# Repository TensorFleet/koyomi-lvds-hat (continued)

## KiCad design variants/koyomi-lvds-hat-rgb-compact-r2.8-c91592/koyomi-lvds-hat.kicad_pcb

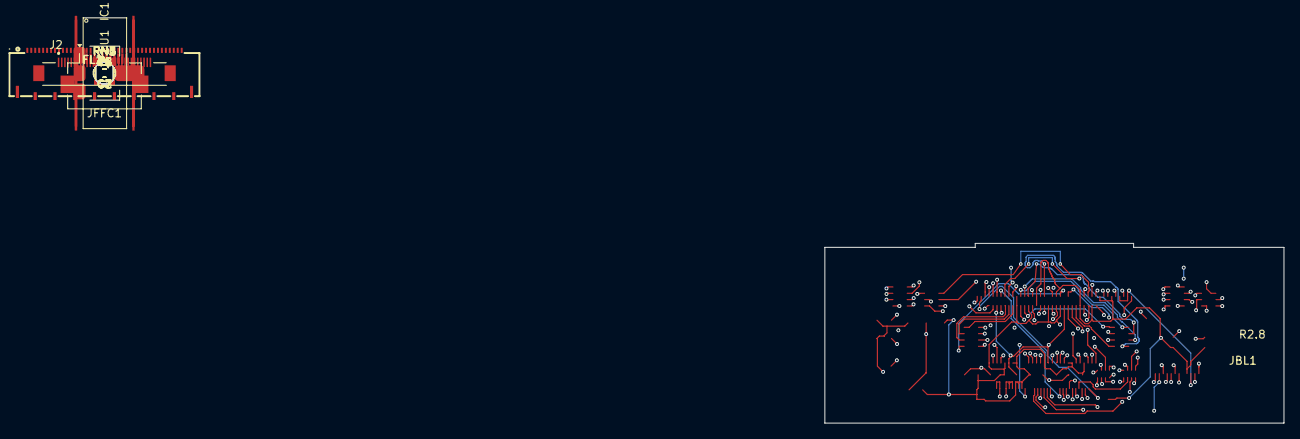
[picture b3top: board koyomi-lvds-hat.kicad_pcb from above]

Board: 4 copper layers, 58.0 x 22.7 mm, 29 parts (0 on the bottom side), 78 nets.

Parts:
C1, C4: 1uF; C_0603_1608Metric_Pad1.08x0.95mm_HandSolder
C2, C5: 100nF; C_0603_1608Metric_Pad1.08x0.95mm_HandSolder
C3, C6: 10nF; C_0603_1608Metric_Pad1.08x0.95mm_HandSolder
C7, C8: 4.7uF; C_0603_1608Metric_Pad1.08x0.95mm_HandSolder
FL1, FL2: DLP2ADN900HL4L; Murata_DLP2ADN121HL4L
H1, H2, H3, H4: MountingHole; RPi_Hat_Mounting_Hole
IC1: SN75LVDS83B; TSSOP56
J2: 20374-R30E-31; I-PEX_20374-R30E-31
JBL1: BACKLIGHT FFC-12; Hirose_FH12-12S-0.5SH_1x12-1MP_P0.50mm_Horizontal
JFFC1: FH41-40S-0.5SH(05) / C596805; FPC-SMD_FH41-40S-0.5SH
JP1: CLKSEL; SolderJumper-2_P1.3mm_Open_RoundedPad1.0x1.5mm
JP2: SHTDN; SolderJumper-2_P1.3mm_Open_RoundedPad1.0x1.5mm
R1, R2: 4.7K; R_0603_1608Metric_Pad0.98x0.95mm_HandSolder
RN1, RN2, RN3, RN4, RN5, RN6: 47; R_Array_Convex_4x0603
U1: AP2114H-2.5; SOT-223-3_TabPin2

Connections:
+2V5: C4.1, C5.1, C6.1, C8.1, J2.4, J2.5, J2.6, U1.2 (VO)
+3V3: C1.1, C2.1, C3.1, C7.1, IC1.1 (IOVCC@1), IC1.9 (VCC@1), IC1.26 (IOVCC@2), IC1.34 (PLLVCC), IC1.44 (LVDSVCC), JFFC1.1 (3.3V), R1.1, R2.1, U1.3 (VI)
+5V: JBL1.10, JFFC1.2 (5V), JFFC1.4 (5V)
B0: JFFC1.7 (BCM4_GPCLK0), RN1.7 (R2.2)
B1: JFFC1.29 (BCM5), RN4.8 (R1.2)
B2: JFFC1.31 (BCM6), RN5.5 (R4.2)
B3: JFFC1.26 (BCM7_CE1), RN3.8 (R1.2)
B4: JFFC1.24 (BCM8_CE0), RN3.7 (R2.2)
B5: JFFC1.21 (BCM9_MISO), RN3.6 (R3.2)
CLKIN: JFFC1.27 (BCM0_ID_SD), RN4.7 (R2.2)
CLKSEL: IC1.17 (CLKSEL), JP1.1 (A), R1.2
D0: IC1.51 (D0), RN5.1 (R1.1)
D1: IC1.52 (D1), RN2.3 (R3.1)
D2: IC1.54 (D2), RN2.2 (R2.1)
D3: IC1.55 (D3), RN6.4 (R4.1)
D4: IC1.56 (D4), RN6.3 (R3.1)
D6: IC1.3 (D6), RN6.2 (R2.1)
D7: IC1.4 (D7), RN3.5 (R4.2)
D8: IC1.6 (D8), RN4.4 (R4.1)
D9: IC1.7 (D9), RN5.3 (R3.1)
D12: IC1.11 (D12), RN5.2 (R2.1)
D13: IC1.12 (D13), RN1.1 (R1.1)
D14: IC1.14 (D14), RN2.4 (R4.1)
D15: IC1.15 (D15), RN1.2 (R2.1)
D18: IC1.19 (D18), RN4.1 (R1.1)
D19: IC1.20 (D19), RN5.4 (R4.1)
D20: IC1.22 (D20), RN3.1 (R1.1)
D21: IC1.23 (D21), RN3.2 (R2.1)
D22: IC1.24 (D22), RN3.3 (R3.1)
D24: IC1.27 (D24), RN1.3 (R3.1)
D25: IC1.28 (D25), RN1.4 (R4.1)
D26: IC1.30 (D26), RN4.3 (R3.1)
EN: JBL1.12, JFFC1.13 (BCM27)
ENABLE: JFFC1.28 (BCM1_ID_SC), RN4.6 (R3.2)
G0: JFFC1.19 (BCM10_MOSI), RN3.4 (R4.1)
G1: JFFC1.23 (BCM11_SCLK), RN4.5 (R4.2)
G2: JFFC1.32 (BCM12_PWM0), RN5.6 (R3.2)
G3: JFFC1.33 (BCM13_PWM1), RN5.7 (R2.2)
G4: JFFC1.8 (BCM14_TXD), RN1.8 (R1.2)
G5: JFFC1.10 (BCM15_RXD), RN2.5 (R4.2)
GND: C1.2, C2.2, C3.2, C4.2, C5.2, C6.2, C7.2, C8.2, IC1.2 (D5), IC1.5 (GND@1), IC1.8 (D10), IC1.10 (D11), IC1.13 (GND@2), IC1.16 (D16), IC1.18 (D17), IC1.21 (GND@3), IC1.25 (D23), IC1.29 (GND@4), IC1.33 (GND@5), IC1.35 (GND@6), IC1.36 (GND@7), IC1.43 (GND@8), IC1.49 (GND@9), IC1.50 (D27), IC1.53 (GND@10), J2.7, J2.8, J2.9, J2.S1 (SHIELD), J2.S2 (SHIELD__1), JBL1.9, JFFC1.6 (GND), JFFC1.9 (GND), JFFC1.14 (GND), JFFC1.20 (GND), JFFC1.25 (GND), JFFC1.30 (GND), JP1.2 (B), JP2.2 (B), U1.1 (GND)
HSYNC: JFFC1.5 (BCM3_SCL), RN1.6 (R3.2)
LCD_INS: J2.30, JFFC1.39 (GND)
L_CLKIN: IC1.31 (CLKIN), RN4.2 (R2.1)
unnamed: FL2.3, IC1.40 (CLCKOUTM)
unnamed: FL2.1, IC1.39 (CLCKOUTP)
unnamed: FL1.7, IC1.48 (Y0M)
unnamed: FL1.5, IC1.47 (Y0P)
unnamed: FL1.3, IC1.46 (Y1M)
unnamed: FL1.1, IC1.45 (Y1P)
unnamed: FL2.7, IC1.42 (Y2M)
unnamed: FL2.5, IC1.41 (Y2P)
PANEL_ID0: J2.10, JFFC1.17 (3.3V)
PANEL_ID1: J2.21, JFFC1.34 (GND)
PWM: JBL1.11, JFFC1.37 (BCM26)
R0: JFFC1.36 (BCM16), RN5.8 (R1.2)
R1: JFFC1.11 (BCM17), RN2.6 (R3.2)
R2: JFFC1.12 (BCM18_PCM_C), RN2.7 (R2.2)
R3: JFFC1.35 (BCM19_MISO_PCM_FS), RN6.5 (R4.2)
R4: JFFC1.38 (BCM20_MOSI_PCM_DI), RN6.6 (R3.2)
R5: JFFC1.40 (BCM21_SCLK_PCM_DO), RN6.7 (R2.2)
RX0+: FL1.6, J2.28
RX0-: FL1.8, J2.29
RX1+: FL1.2, J2.26
RX1-: FL1.4, J2.27
RX2+: FL2.6, J2.24
RX2-: FL2.8, J2.25
RXCLK+: FL2.2, J2.22
RXCLK-: FL2.4, J2.23
SHTDN: IC1.32 (~SHTDN), JP2.1 (A), R2.2
VAD: J2.1, J2.2, JBL1.7
VCD1: J2.18, JBL1.6
VCD2: J2.17, JBL1.5
VCD3: J2.16, JBL1.4
VCD4: J2.15, JBL1.3
VCD5: J2.14, JBL1.2
VCD6: J2.13, JBL1.1
VSYNC: JFFC1.3 (BCM2_SDA), RN1.5 (R4.2)

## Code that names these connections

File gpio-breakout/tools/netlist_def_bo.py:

"""GPIO breakout: FH41-40S FFC (carrier JDISP1/JFFC1 system) <-> Pi 40-pin header.

Straight-through pins 1..40 EXCEPT 17/34/39, which are isolated behind solder
jumpers: on a stock Pi those pins are 3V3/GND/GND, but the FFC system assigns
them PANEL_ID0/PANEL_ID1/LCD_INS. Jumpers default OPEN; test pads expose the
FFC-side nets for strapping or probing.
"""

NC = '__NC__'

# Pi header net names, physical pins 1..40 (standard map)
PI = {
    1: '+3V3', 2: '+5V', 3: 'GPIO2', 4: '+5V', 5: 'GPIO3', 6: 'GND',
    7: 'GPIO4', 8: 'GPIO14', 9: 'GND', 10: 'GPIO15', 11: 'GPIO17', 12: 'GPIO18',
    13: 'GPIO27', 14: 'GND', 15: 'GPIO22', 16: 'GPIO23', 17: '+3V3', 18: 'GPIO24',
    19: 'GPIO10', 20: 'GND', 21: 'GPIO9', 22: 'GPIO25', 23: 'GPIO11', 24: 'GPIO8',
    25: 'GND', 26: 'GPIO7', 27: 'ID_SD', 28: 'ID_SC', 29: 'GPIO5', 30: 'GND',
    31: 'GPIO6', 32: 'GPIO12', 33: 'GPIO13', 34: 'GND', 35: 'GPIO19', 36: 'GPIO16',
    37: 'GPIO26', 38: 'GPIO20', 39: 'GND', 40: 'GPIO21',
}
SPECIAL = {17: 'PANEL_ID0', 34: 'PANEL_ID1', 39: 'LCD_INS'}

ffc_map = {}
for n in range(1, 41):
    ffc_map[str(n)] = SPECIAL.get(n, PI[n])
ffc_map['1'] = '+3V3_FFC'
ffc_map['2'] = '+5V_FFC'
ffc_map['4'] = '+5V_FFC'
for n in range(41, 50):          # shield / mounting pins
    ffc_map[str(n)] = 'GND'

hdr_map = {str(n): PI[n] for n in range(1, 41)}

COMPONENTS = [
    ('J1', 'B2_INTERCONNECT:FH41-40S-0.5SH', 'FH41-40S-0.5SH(05)',
     'B2_INTERCONNECT:FPC-SMD_FH41-40S-0.5SH', ffc_map,
     {'lcsc': 'C596805', 'desc': 'carrier/LCD system FFC, bottom contact'}),
    ('J2', 'Connector_Generic:Conn_02x20_Odd_Even', 'Pi GPIO 2x20',
     'Connector_PinHeader_2.54mm:PinHeader_2x20_P2.54mm_Vertical', hdr_map,
     {'desc': 'fit stacking socket to ride a Pi, or pin header for cables'}),
    ('JP1', 'Jumper:SolderJumper_2_Open', 'ID0-3V3',
     'Jumper:SolderJumper-2_P1.3mm_Open_RoundedPad1.0x1.5mm',
     {'1': 'PANEL_ID0', '2': '+3V3'}, {'desc': 'close = FFC17 to Pi 3V3 (STRAP HIGH)'}),
    ('JP2', 'Jumper:SolderJumper_2_Open', 'ID1-GND',
     'Jumper:SolderJumper-2_P1.3mm_Open_RoundedPad1.0x1.5mm',
     {'1': 'PANEL_ID1', '2': 'GND'}, {'desc': 'close = FFC34 to GND (STRAP LOW)'}),
    ('JP3', 'Jumper:SolderJumper_2_Open', 'INS-GND',
     'Jumper:SolderJumper-2_P1.3mm_Open_RoundedPad1.0x1.5mm',
     {'1': 'LCD_INS', '2': 'GND'}, {'desc': 'close = FFC39 to GND (report inserted)'}),
    ('F1', 'Device:Polyfuse', '0.5A polyfuse 1206',
     'Fuse:Fuse_1206_3216Metric', {'1': '+5V_LNK', '2': '+5V_FFC'},
     {'lcsc': 'C106264', 'desc': 'PTC resettable, 0.5 A hold — FFC contact rating (SMD1206P050TF/15; alt C315893)'}),
    ('JP4', 'Jumper:SolderJumper_2_Bridged', '5V LINK',
     'Jumper:SolderJumper-2_P1.3mm_Bridged_RoundedPad1.0x1.5mm',
     {'1': '+5V', '2': '+5V_LNK'}, {'desc': 'CUT when LCD chain is powered externally'}),
    ('JP5', 'Jumper:SolderJumper_2_Bridged', '3V3 LINK',
     'Jumper:SolderJumper-2_P1.3mm_Bridged_RoundedPad1.0x1.5mm',
     {'1': '+3V3', '2': '+3V3_FFC'}, {'desc': 'CUT when LCD chain is powered externally'}),
    ('TP1', 'Connector:TestPoint', 'PANEL_ID0',
     'TestPoint:TestPoint_Pad_1.5x1.5mm', {'1': 'PANEL_ID0'}, {}),
    ('TP2', 'Connector:TestPoint', 'PANEL_ID1',
     'TestPoint:TestPoint_Pad_1.5x1.5mm', {'1': 'PANEL_ID1'}, {}),
    ('TP3', 'Connector:TestPoint', 'LCD_INS',
     'TestPoint:TestPoint_Pad_1.5x1.5mm', {'1': 'LCD_INS'}, {}),
    ('TP4', 'Connector:TestPoint', 'GND',
     'TestPoint:TestPoint_Pad_1.5x1.5mm', {'1': 'GND'}, {}),
    ('TP5', 'Connector:TestPoint', '3V3',
     'TestPoint:TestPoint_Pad_1.5x1.5mm', {'1': '+3V3'}, {}),
    ('H1', 'Mechanical:MountingHole', 'M2.5',
     'MountingHole:MountingHole_2.7mm_M2.5', None, {}),
    ('H2', 'Mechanical:MountingHole', 'M2.5',
     'MountingHole:MountingHole_2.7mm_M2.5', None, {}),
]

PWR_FLAGS = [
    ('#FLG1', '+3V3'), ('#FLG2', '+5V'), ('#FLG3', 'GND'),
]

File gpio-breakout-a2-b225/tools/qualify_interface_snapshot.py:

"""Independent schematic XML versus native PCB-pad qualification."""
import hashlib,json,xml.etree.ElementTree as ET
from pathlib import Path
D=Path(__file__).resolve().parents[1];r=json.loads((D/'reports/qualification-native-snapshot.json').read_text());sch={}
for net in ET.parse(D/'reports/qualification-netlist.xml').findall('.//nets/net'):
 for node in net.findall('node'):sch[node.attrib['ref'],node.attrib['pin']]=net.attrib['name']
pcb={};pads={}
for ref,f in r['footprints'].items():
 for p in f['definition']['items']:
  if p['@type'].endswith('.Pad') and p.get('number'):pcb[ref,p['number']]=p.get('net',{}).get('name','');pads[ref,p['number']]=p
errors=[]
for key,net in pcb.items():
 sn=sch.get(key,'')
 if net and net!=sn:errors.append({'pad':key,'pcb':net,'schematic':sn})
 if not net and sn and not sn.startswith('unconnected-'):errors.append({'pad':key,'pcb':net,'schematic':sn})
ffc=['USB_VBUS']*4+['GND','USB_D_N','USB_D_P','GND','+5V_FFC','+5V_FFC','+3V3_FFC','GND','GPIO23','GPIO24','ID_SC','GPIO2','GPIO3','GND','ID_SD','GND']+[f'GPIO{i}' for i in range(4,10)]+['GND']+[f'GPIO{i}' for i in range(10,16)]+['GND']+[f'GPIO{i}' for i in range(16,22)]
for n,net in enumerate(ffc,1):
 if pcb.get(('J1',str(n)))!=net:errors.append({'ffc_pin':n,'expected':net,'actual':pcb.get(('J1',str(n)))})
j1=[p for p in r['footprints']['J1']['definition']['items'] if p['@type'].endswith('.Pad')];paste=sum('BL_F_Paste' in p['pad_stack']['layers'] for p in j1)
checks={'numbered_pad_netlist_parity':not errors,'forty_pin_contract':len(ffc)==40,'J1_paste_all_42_pads':paste==42,'USB_supply_separate_from_LCD':all(pcb['J1',str(n)]=='USB_VBUS' for n in range(1,5)) and pcb['J1','9']=='+5V_FFC' and pcb['J1','11']=='+3V3_FFC','independent_CC_pull_downs':pcb['J3','A5']==pcb['R1','1']=='USB_CC1' and pcb['J3','B5']==pcb['R2','1']=='USB_CC2' and pcb['R1','2']==pcb['R2','2']=='GND','PTC_then_slew_switch_then_reverse_blocker':pcb['J3','A4']==pcb['F2','1']=='USB_VBUS_RAW' and pcb['F2','2']==pcb['U4','1']==pcb['U4','3']=='USB_VBUS_IN' and pcb['U4','6']==pcb['U1','1']==pcb['C4','1']=='USB_VBUS_SOFT' and pcb['U4','4']==pcb['C3','1']=='USB_SLEW_CT' and pcb['U1','6']==pcb['J1','1']=='USB_VBUS'}
checks['U4_QOD_unconnected']=pcb['U4','5'].startswith('unconnected-')
components={c.attrib['ref']:c for c in ET.parse(D/'reports/qualification-netlist.xml').findall('.//components/comp')}
def field(ref,name):
 return next((v.text for v in components[ref].findall('fields/field') if v.attrib.get('name')==name),None)
checks['CT_10n_C0G_part']=field('C3','LCSC')=='C76599' and components['C3'].findtext('value')=='10n 50V C0G 5%'
checks['correct_zero_ohm_array_population']=all(field('RN'+str(i),'LCSC')=='C1952' and components['RN'+str(i)].findtext('value').startswith('0R') for i in range(1,7))
checks['correct_load_switch_identity']=field('U4','LCSC')=='C131941'
result={'passed':all(checks.values()),'checks':checks,'errors':errors,'numbered_board_pads_checked':len(pcb),'FFC_contacts':len(ffc),'J1_paste_pads':paste,'board_sha256':r['board_sha256'],'schematic_sha256':hashlib.sha256((D/'gpio_breakout.kicad_sch').read_bytes()).hexdigest(),'netlist_sha256':hashlib.sha256((D/'reports/qualification-netlist.xml').read_bytes()).hexdigest(),'FFC_pin_map':{str(n):net for n,net in enumerate(ffc,1)},'release_ready':False,'limits':'Connectivity proves topology, not dynamic reverse-blocking performance, inrush, host current allocation, cable mating or DPI timing.'}
(D/'reports/qualification-interface.json').write_text(json.dumps(result,indent=2)+'\n');print(json.dumps({k:v for k,v in result.items() if k!='FFC_pin_map'},indent=2))
if not result['passed']:raise SystemExit(2)
